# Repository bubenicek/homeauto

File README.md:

# homeauto
Home automation projects

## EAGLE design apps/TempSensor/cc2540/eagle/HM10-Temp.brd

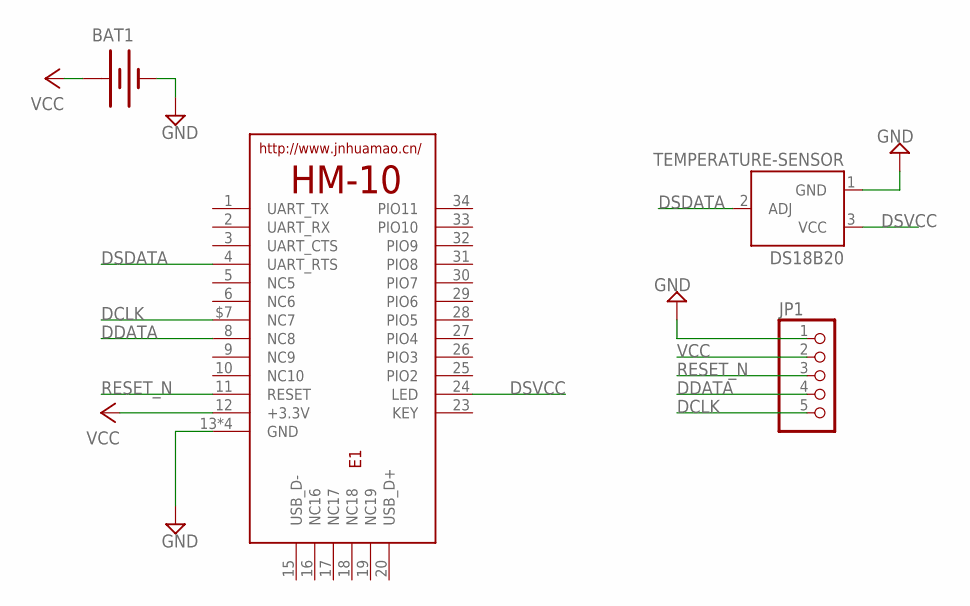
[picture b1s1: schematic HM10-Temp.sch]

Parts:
BAT1: BATTERY20PTH; BATTCOM_20MM_PTH
DS18B20: TEMPERATURE-SENSOR; TO-92
E1: HM-10-BOARD; 26.9X13X2.2_BOARD
JP1: PINHD-1X5; 1X05

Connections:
DCLK: E1.$7 (NC7), JP1.5
DDATA: E1.8 (NC8), JP1.4
DSDATA: DS18B20.2 (ADJ), E1.4 (UART_RTS)
DSVCC: DS18B20.3 (VCC), E1.24 (LED)
GND: BAT1.2 (-), DS18B20.1 (GND), E1.13 (GND), E1.14 (GND), E1.21 (GND), E1.22 (GND), JP1.1
RESET_N: E1.11 (RESET), JP1.3
VCC: BAT1.1 (+), E1.12 (+3.3V), JP1.2

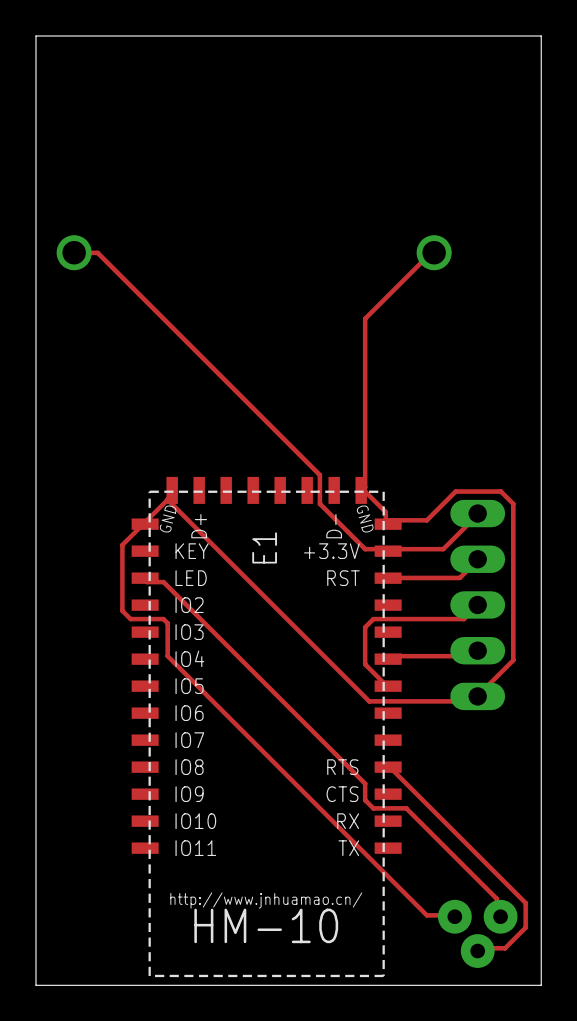
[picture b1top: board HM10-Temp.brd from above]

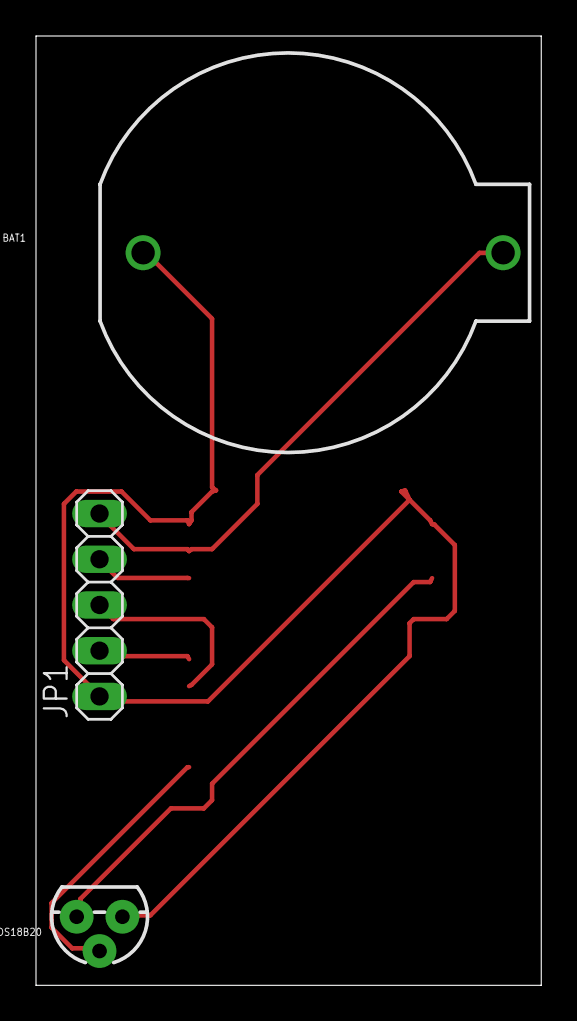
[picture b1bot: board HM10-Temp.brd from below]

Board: 2 copper layers, 28.1 x 52.7 mm, 4 parts (3 on the bottom side), 7 nets.

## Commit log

2021-12-08 Added sources

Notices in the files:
parts and their libraries:
SparkFun-Electromechanical: Licensing: Creative Commons ShareAlike 4.0 International - https://creativecommons.org/licenses/by-sa/4.0
